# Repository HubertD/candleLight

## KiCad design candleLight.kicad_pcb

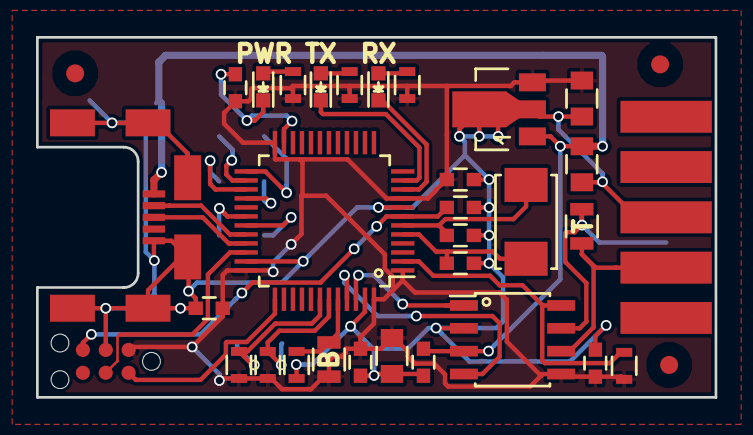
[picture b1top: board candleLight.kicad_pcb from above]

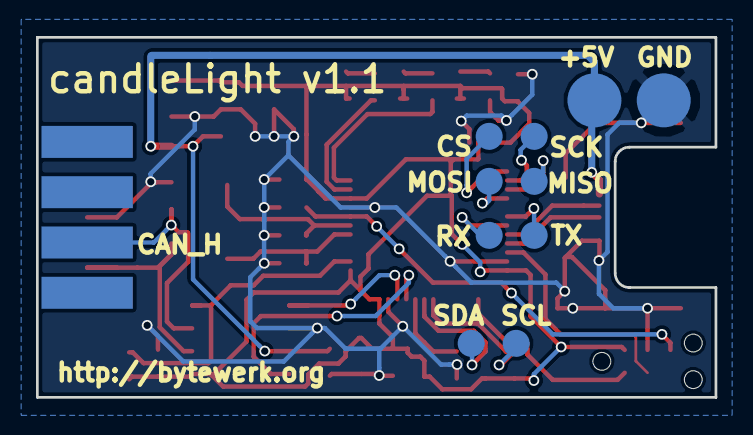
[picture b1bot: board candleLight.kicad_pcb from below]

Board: 2 copper layers, 37.7 x 20.0 mm, 44 parts (10 on the bottom side), 29 nets.

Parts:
C201, C202: 20pF; C_0603
C203, C204, C205, C206, C208, C402, C403: 100nF; C_0603
C207, C301, C303: 10uF; C_0805
CS: TEST_1P; Measurement_Point_Round-SMD-Pad_Small
D601, D602, D603: LED; LED_0603
FID101, FID102, FID103: Dummy_FIDUCIAL_Passermarke_Type1_RevE_Date16Nov20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; Fiducial_1mm_Dia_2.54mm_Outer_CopperTop
MISO: TEST_1P; Measurement_Point_Round-SMD-Pad_Small
MOSI: TEST_1P; Measurement_Point_Round-SMD-Pad_Small
P501: USB_OTG; Molex-Micro-USB-B-Middle-Mount
R201, R202: 4K7; R_0603
R203: R; R_0805
R204, R601, R602, R603: 1K; R_0603
R401: 10K; R_0603
R402: dnp; R_0805
RX: TEST_1P; Measurement_Point_Round-SMD-Pad_Small
SCK: TEST_1P; Measurement_Point_Round-SMD-Pad_Small
SCL: TEST_1P; Measurement_Point_Round-SMD-Pad_Small
SDA: TEST_1P; Measurement_Point_Round-SMD-Pad_Small
TX: TEST_1P; Measurement_Point_Round-SMD-Pad_Small
U201: STM32F072C8Tx; LQFP-48_7x7mm_Pitch0.5mm
U301: MCP1754ST-3302E/MB; SOT89-3_Housing
U401: TJA1051/3; SOIC-8_3.9x4.9mm_Pitch1.27mm
W301, W302: TEST_1P; Measurement_Point_Round-SMD-Pad_Big
X501: CON_SWD; TC2030-NL
X502: SUB-D9; DB9M_CI
Y201: 8MHz; ABM3

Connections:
+3V3: C203.1, C204.1, C205.1, C206.1, C207.1, C303.1, C403.1, R201.1, R202.2, R203.1, R401.1, R601.2, R602.2, R603.2, U201.1, U201.9, U201.24, U201.36, U201.48, U301.3, U401.5, X501.1
+5V: C301.1, C402.1, P501.1, U301.1, U401.3, W301.1
/CAN/CAN_H: R402.1, U401.7, X502.7
/CAN/CAN_L: R402.2, U401.6, X502.2
/CAN/CAN_S: R401.2, U201.2, U401.8
/Connectors/NRST: C208.1, U201.7, X501.5
/Connectors/SWCLK: U201.37, X501.2
/Connectors/SWDIO: U201.34, X501.4
/Connectors/USB_DM: P501.2, U201.32
/Connectors/USB_DP: P501.3, U201.33
/LEDs/LED1: D601.1, U201.10
/LEDs/LED2: D602.1, U201.11
/MCU/BOOT0: R203.2, R204.2, U201.44
/MCU/CAN_RX: U201.45, U401.4
/MCU/CAN_TX: U201.46, U401.1
GND: C201.1, C202.1, C203.2, C204.2, C205.2, C206.2, C207.2, C208.2, C301.2, C303.2, C402.2, C403.2, D603.1, P501.5, P501.6, R204.1, U201.8, U201.23, U201.35, U201.47, U301.2, U401.2, W302.1, X501.3, X502.3
unnamed: C201.2, U201.5, Y201.1
unnamed: C202.2, U201.6, Y201.2
unnamed: D601.2, R601.1
unnamed: D602.2, R602.1
unnamed: D603.2, R603.1
unnamed: R201.2, SCL.1, U201.42
unnamed: R202.1, SDA.1, U201.43
unnamed: CS.1, U201.25
unnamed: SCK.1, U201.26
unnamed: MISO.1, U201.27
unnamed: MOSI.1, U201.28
unnamed: TX.1, U201.30
unnamed: RX.1, U201.31

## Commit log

2016-03-26 first checkin
2016-03-26 add cache file
2016-03-28 set subd9 pin 3 to gnd, correct solder mask margin
2016-03-29 rename con.sch to connectors.sch (allow checkout in windows)
2016-03-29 add missing usb data line resistors
2016-03-30 remove references to old libs
2016-03-30 add fiducials
2016-03-30 adjust +3v3 plane settings
2016-04-16 add license (CERN OHL v1.2)
2016-04-28 remove unneeded parts
2016-04-28 add testpoints, reset line cap
2016-04-28 candleLight v1.2
2016-04-28 new measurements
2016-04-29 optimize
2016-04-29 fine tuning
2016-04-29 v1.1
2016-04-29 create BOM
2016-04-29 render images
2016-04-29 add export files for v1.1
2016-05-12 move gerber panel files to own dir
2016-05-12 change placement texts
2016-05-12 add panel pcb
2016-05-12 add placement.pdf
2016-05-12 add single board pick&place file
2022-07-28 Add 3D-printable case
    This is a FreeCAD model of a 3d-printable case for the candlelight.
    It is intended to be printed with ABS or PETG and to mechanically
    protect the candlelight.
    Boths halfs can be screwed together using 2 or 4 M3x8mm cylinder head
    scrwes.
    LEDs are still somewhat visible through holes in the upper part of the
